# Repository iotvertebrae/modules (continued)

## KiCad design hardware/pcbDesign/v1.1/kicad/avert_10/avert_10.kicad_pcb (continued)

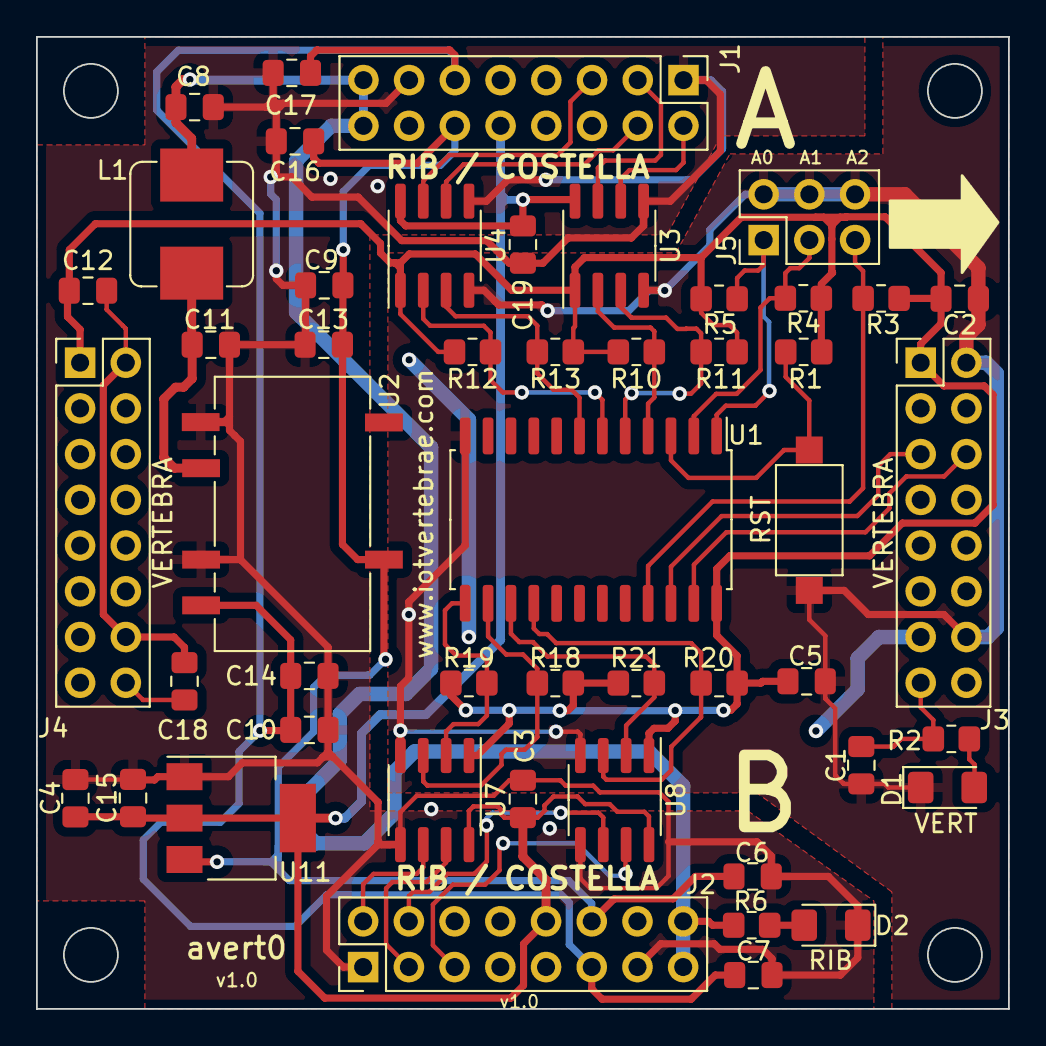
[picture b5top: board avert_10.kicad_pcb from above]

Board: 4 copper layers, 54.0 x 54.0 mm, 49 parts (0 on the bottom side), 42 nets.

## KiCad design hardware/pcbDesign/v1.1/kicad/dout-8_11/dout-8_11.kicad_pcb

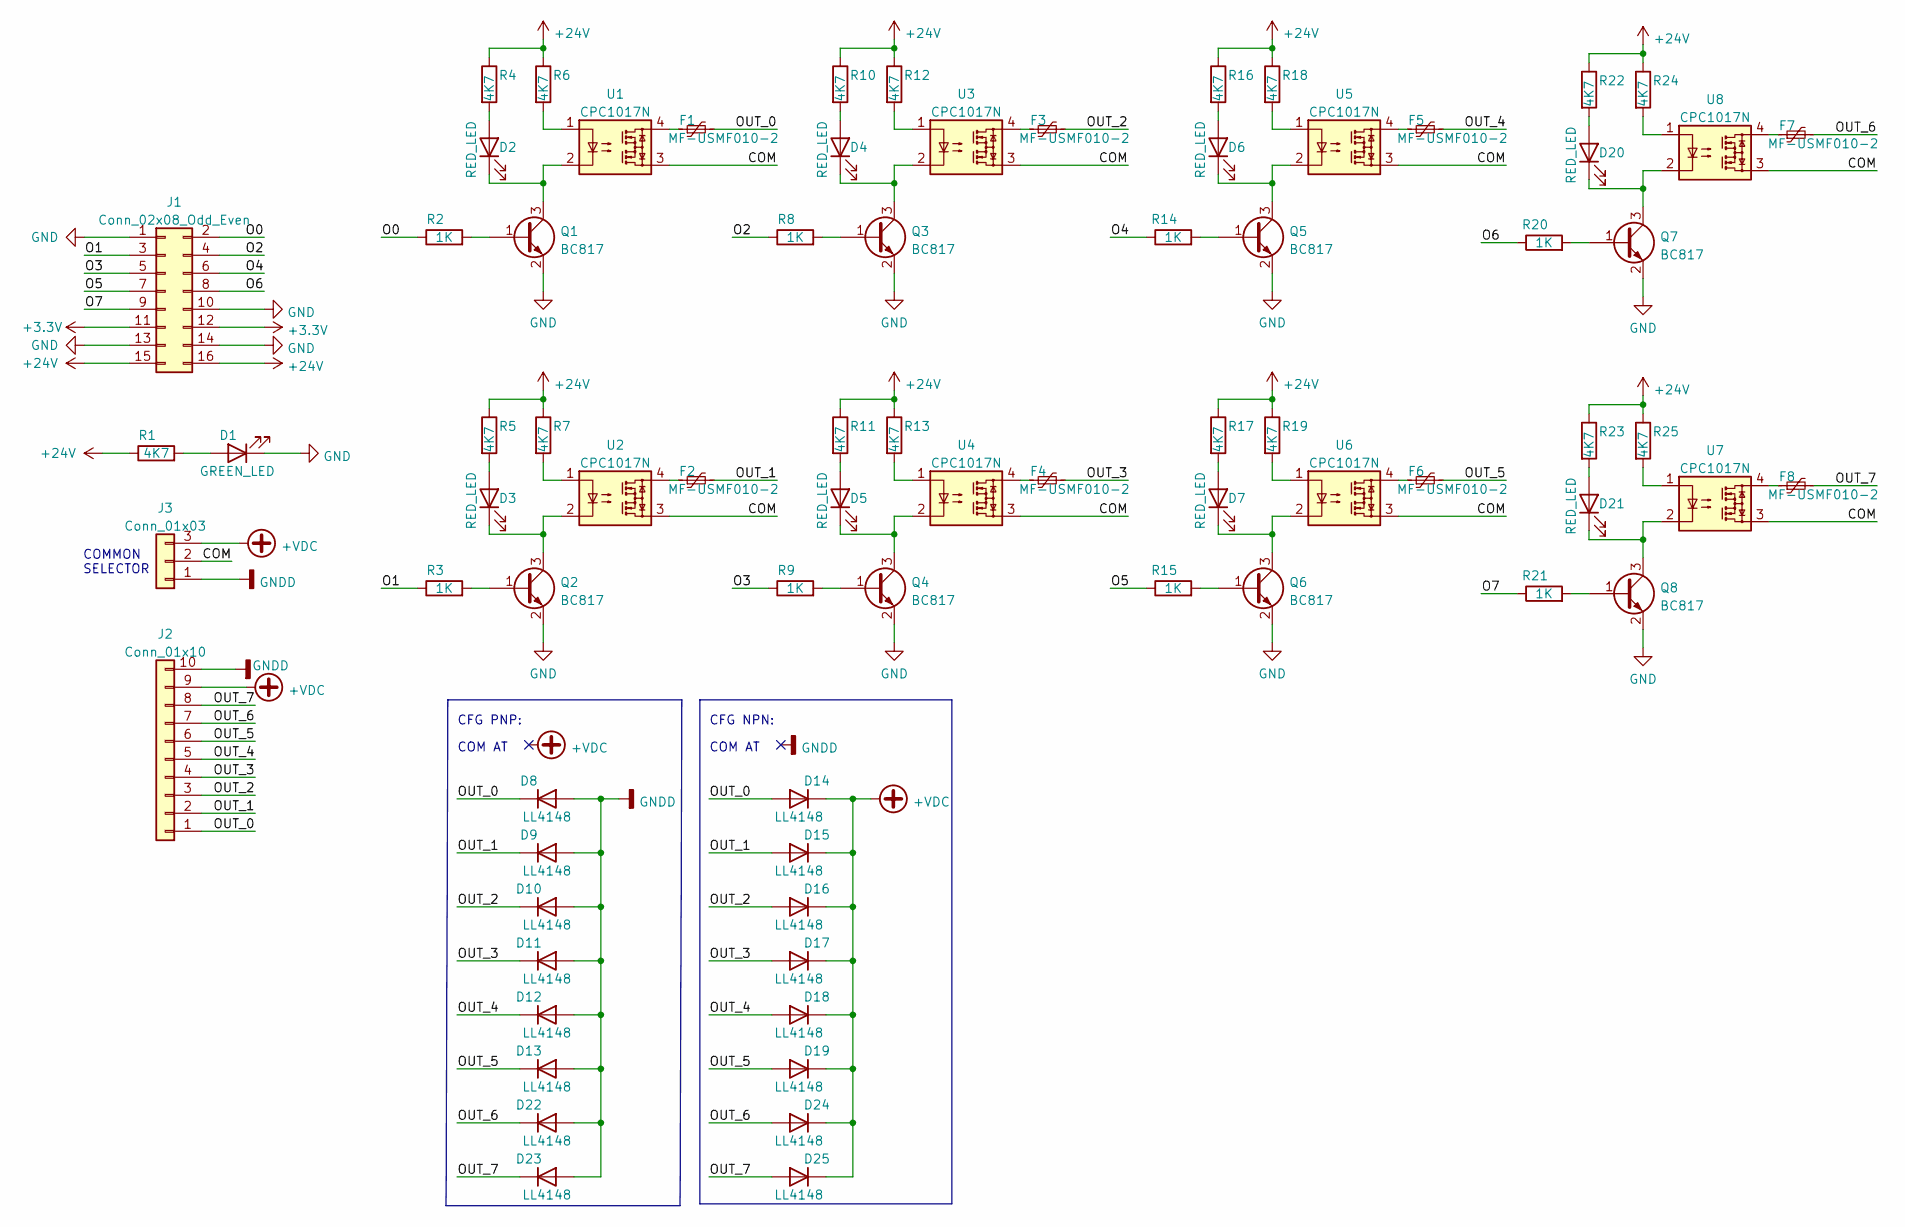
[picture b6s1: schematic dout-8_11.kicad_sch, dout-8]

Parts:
D1: GREEN_LED; LED_1206_3216Metric_Pad1.42x1.75mm_HandSolder
D2, D3, D4, D5, D6, D7, D20, D21: RED_LED; LED_1206_3216Metric_Pad1.42x1.75mm_HandSolder
D8, D9, D10, D11, D12, D13, D14, D15, D16, D17, D18, D19, D22, D23, D24, D25: LL4148; D_MiniMELF
F1, F2, F3, F4, F5, F6, F7, F8: MF-USMF010-2; Fuse_1210_3225Metric_Pad1.42x2.65mm_HandSolder
J1: Conn_02x08_Odd_Even; PinHeader_2x08_P2.54mm_Vertical
J2: Conn_01x10; PhoenixContact_MSTBA_2,5_10-G-5,08_1x10_P5.08mm_Horizontal
J3: Conn_01x03; PinHeader_1x03_P2.54mm_Vertical
Q1, Q2, Q3, Q4, Q5, Q6, Q7, Q8: BC817; SOT-23
R1, R4, R5, R6, R7, R10, R11, R12, R13, R16, R17, R18, R19, R22, R23, R24, R25: 4K7; R_0805_2012Metric_Pad1.20x1.40mm_HandSolder
R2, R3, R8, R9, R14, R15, R20, R21: 1K; R_0805_2012Metric_Pad1.20x1.40mm_HandSolder
U1, U2, U3, U4, U5, U6, U7, U8: CPC1017N; SOP-4_3.8x4.1mm_P2.54mm

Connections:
+3.3V: J1.11, J1.12
+24V: J1.15, J1.16, R1.1, R4.1, R5.1, R6.1, R7.1, R10.1, R11.1, R12.1, R13.1, R16.1, R17.1, R18.1, R19.1, R22.1, R23.1, R24.1, R25.1
+VDC: D14.1 (K), D15.1 (K), D16.1 (K), D17.1 (K), D18.1 (K), D19.1 (K), D24.1 (K), D25.1 (K), J2.9, J3.3
/COM: J3.2, U1.3, U2.3, U3.3, U4.3, U5.3, U6.3, U7.3, U8.3
/O0: J1.2, R2.1
/O1: J1.3, R3.1
/O2: J1.4, R8.1
/O3: J1.5, R9.1
/O4: J1.6, R14.1
/O5: J1.7, R15.1
/O6: J1.8, R20.1
/O7: J1.9, R21.1
/OUT_0: D8.1 (K), D14.2 (A), F1.2, J2.1
/OUT_1: D9.1 (K), D15.2 (A), F2.2, J2.2
/OUT_2: D10.1 (K), D16.2 (A), F3.2, J2.3
/OUT_3: D11.1 (K), D17.2 (A), F4.2, J2.4
/OUT_4: D12.1 (K), D18.2 (A), F5.2, J2.5
/OUT_5: D13.1 (K), D19.2 (A), F6.2, J2.6
/OUT_6: D22.1 (K), D24.2 (A), F7.2, J2.7
/OUT_7: D23.1 (K), D25.2 (A), F8.2, J2.8
GND: D1.1 (K), J1.1, J1.10, J1.13, J1.14, Q1.2 (E), Q2.2 (E), Q3.2 (E), Q4.2 (E), Q5.2 (E), Q6.2 (E), Q7.2 (E), Q8.2 (E)
GNDD: D8.2 (A), D9.2 (A), D10.2 (A), D11.2 (A), D12.2 (A), D13.2 (A), D22.2 (A), D23.2 (A), J2.10, J3.1
unnamed: D1.2 (A), R1.2
unnamed: D2.1 (K), Q1.3 (C), U1.2
unnamed: D2.2 (A), R4.2
unnamed: D3.1 (K), Q2.3 (C), U2.2
unnamed: D3.2 (A), R5.2
unnamed: D4.1 (K), Q3.3 (C), U3.2
unnamed: D4.2 (A), R10.2
unnamed: D5.1 (K), Q4.3 (C), U4.2
unnamed: D5.2 (A), R11.2
unnamed: D6.1 (K), Q5.3 (C), U5.2
unnamed: D6.2 (A), R16.2
unnamed: D7.1 (K), Q6.3 (C), U6.2
unnamed: D7.2 (A), R17.2
unnamed: D20.1 (K), Q7.3 (C), U8.2
unnamed: D20.2 (A), R22.2
unnamed: D21.1 (K), Q8.3 (C), U7.2
unnamed: D21.2 (A), R23.2
unnamed: F1.1, U1.4
unnamed: F2.1, U2.4
unnamed: F3.1, U3.4
unnamed: F4.1, U4.4
unnamed: F5.1, U5.4
unnamed: F6.1, U6.4
unnamed: F7.1, U8.4
unnamed: F8.1, U7.4
unnamed: Q1.1 (B), R2.2
unnamed: Q2.1 (B), R3.2
unnamed: Q3.1 (B), R8.2
unnamed: Q4.1 (B), R9.2
unnamed: Q5.1 (B), R14.2
unnamed: Q6.1 (B), R15.2
unnamed: Q7.1 (B), R20.2
unnamed: Q8.1 (B), R21.2
unnamed: R6.2, U1.1
unnamed: R7.2, U2.1
unnamed: R12.2, U3.1
unnamed: R13.2, U4.1
unnamed: R18.2, U5.1
unnamed: R19.2, U6.1
unnamed: R24.2, U8.1
unnamed: R25.2, U7.1

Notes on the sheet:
COMMON SELECTOR
CFG NPN:
COM AT
CFG PNP:

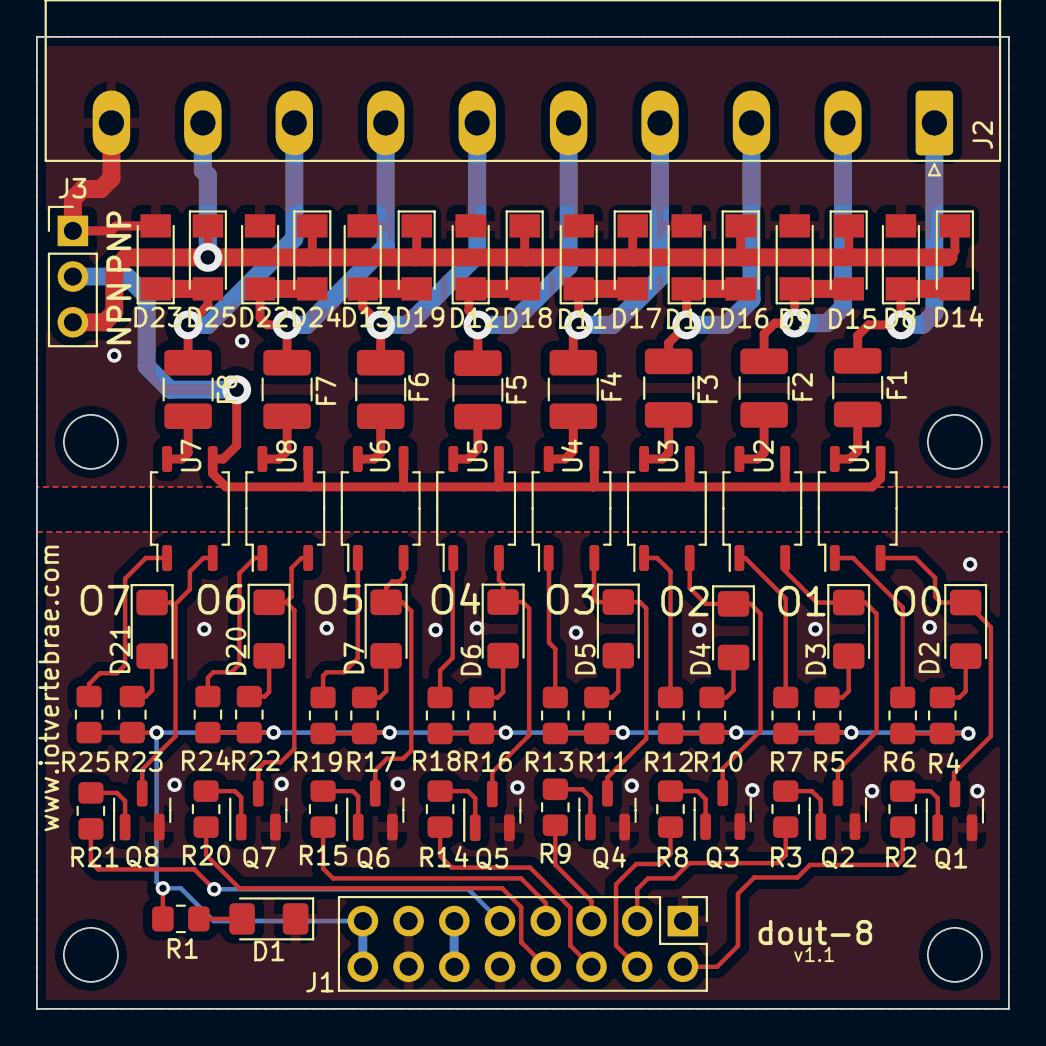
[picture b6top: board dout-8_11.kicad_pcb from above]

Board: 2 copper layers, 54.0 x 54.0 mm, 77 parts (0 on the bottom side), 63 nets.
